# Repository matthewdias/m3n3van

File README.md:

# m3n3van
 
- The rev1 pcb supports a lot of different layouts. This was mostly an exercise for me and a way to make some unique bottom rows available that wouldn't exist otherwise. As a result it has a few issues, a missing switch, and lots of conflicts with screw holes, necessitating switch rotation.

- The rev2 pcb is a return to the original idea of simply a minivan with 2x3u split space.

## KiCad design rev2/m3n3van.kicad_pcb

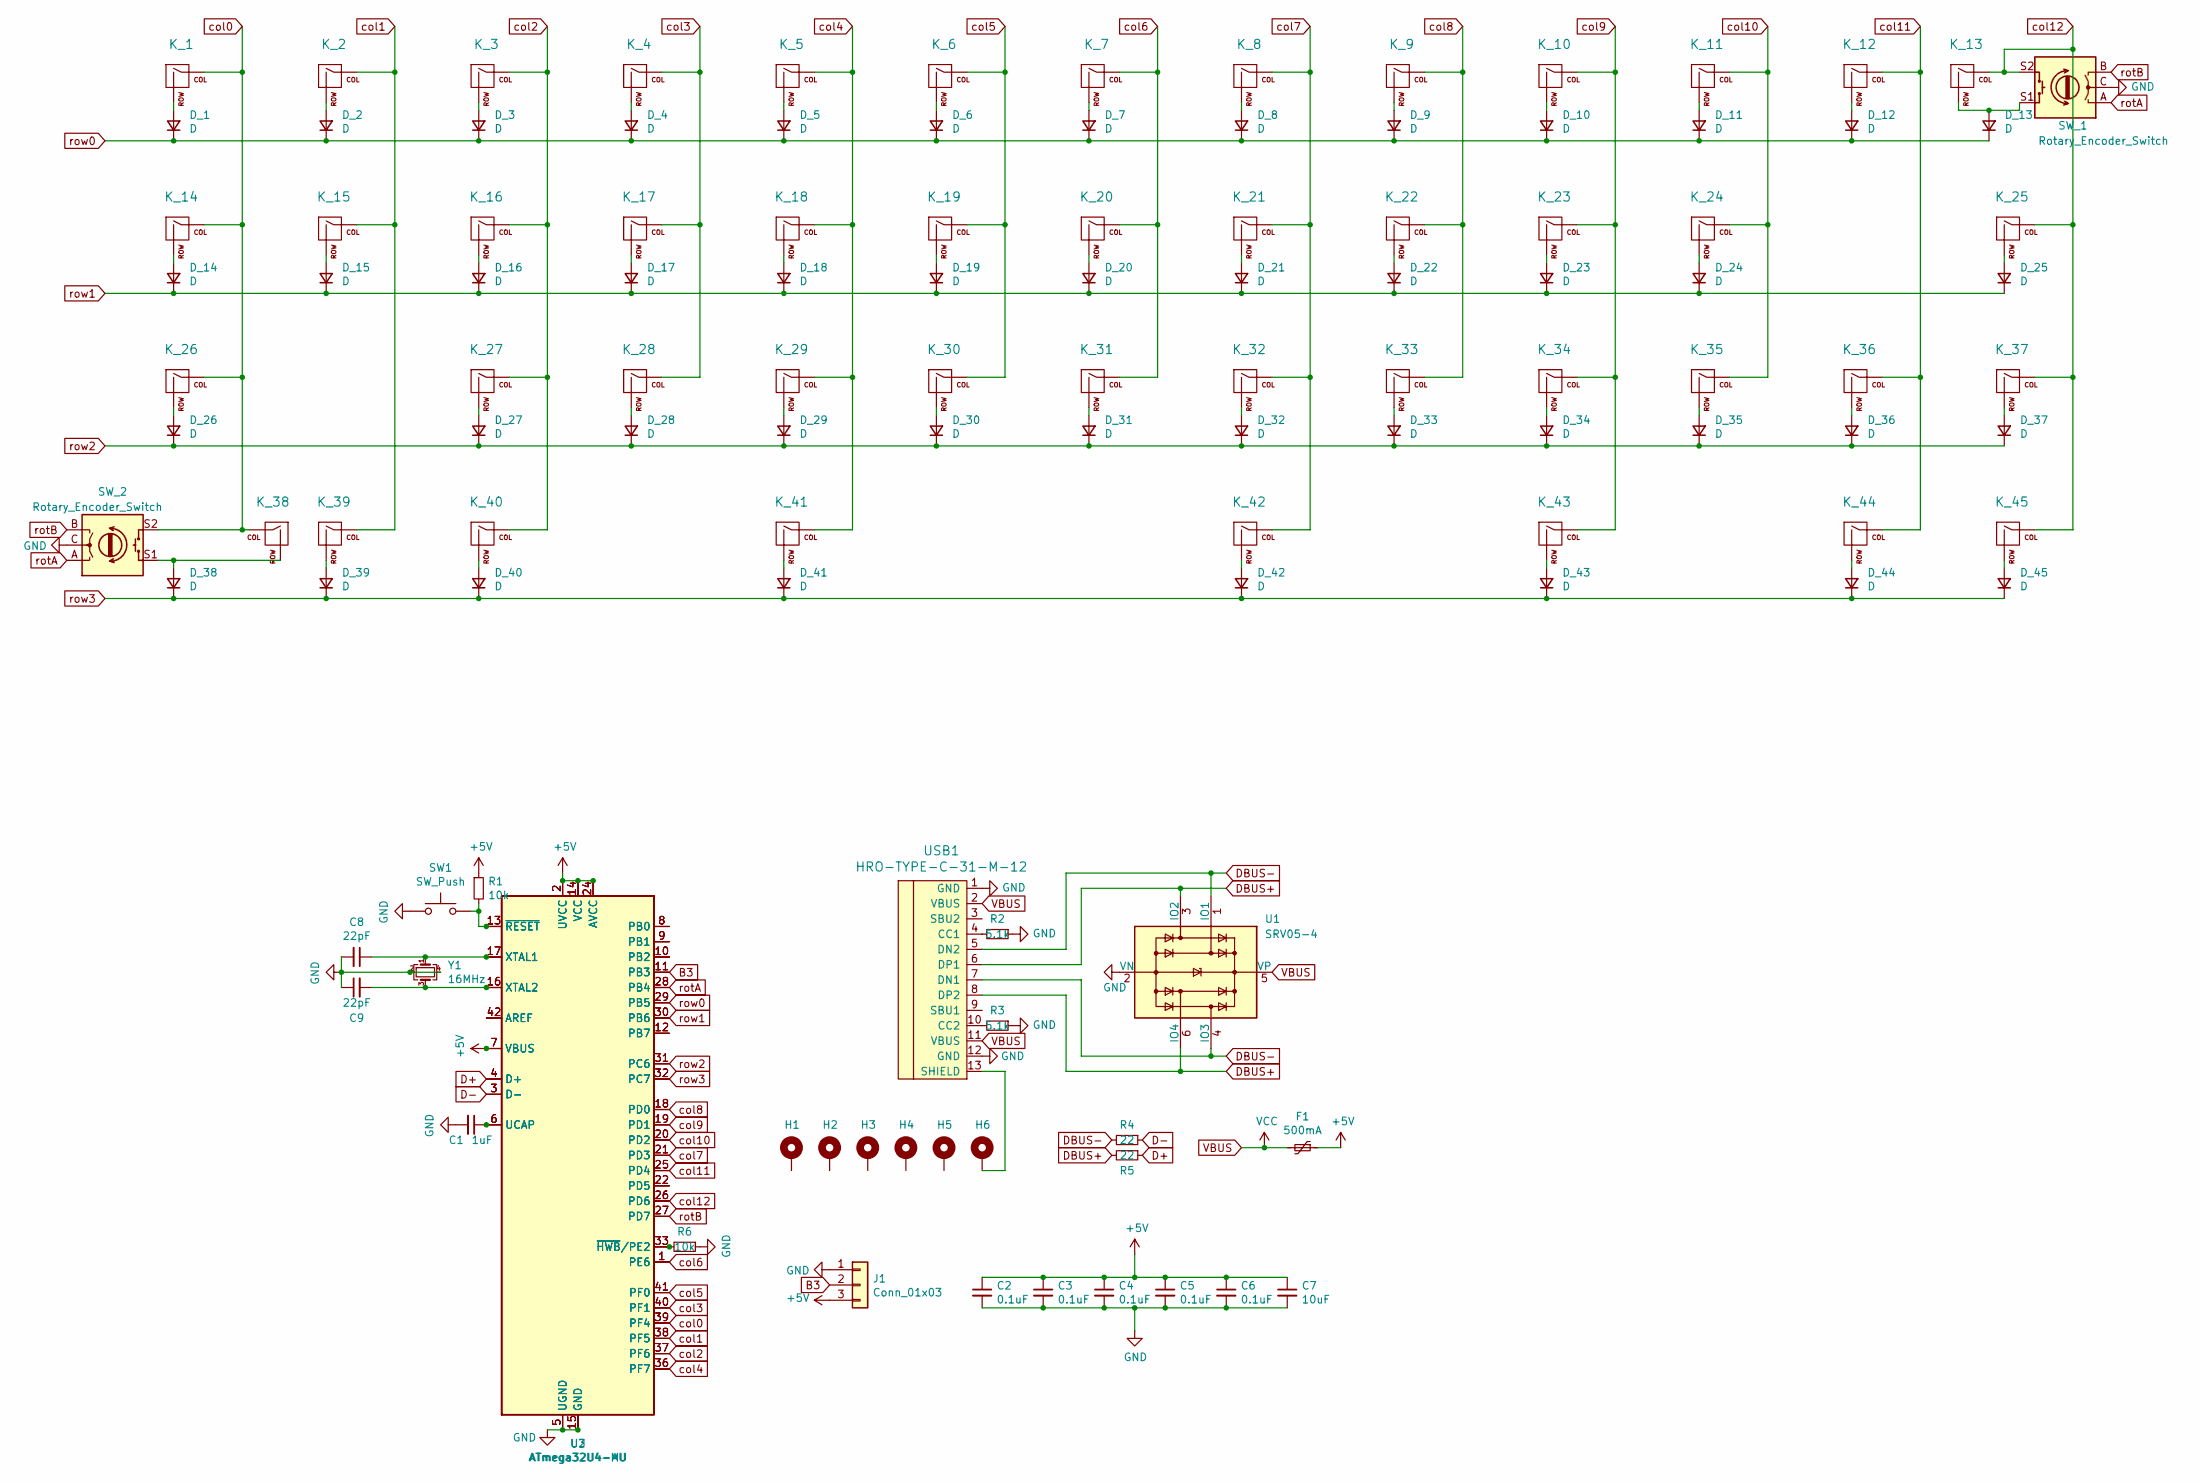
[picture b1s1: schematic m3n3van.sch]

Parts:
C1: 1uF; C_0603_1608Metric
C2, C3, C4, C5, C6: 0.1uF; C_0603_1608Metric
C7: 10uF; C_0603_1608Metric
C8, C9: 22pF; C_0603_1608Metric
D_1, D_2, D_3, D_4, D_5, D_6, D_7, D_8, D_9, D_10, D_11, D_12, D_13, D_14, D_15, D_16, D_17, D_18, D_19, D_20, D_21, D_22, D_23, D_24, D_25, D_26, D_27, D_28, D_29, D_30, D_31, D_32, D_33, D_34, D_35, D_36, D_37, D_38, D_39, D_40, D_41, D_42, D_43, D_44, D_45: D; D_SOD-123
F1: 500mA; Fuse_1206_3216Metric
H1, H2, H3, H4, H5, H6: MountingHole_Pad; MountingHole_2.2mm_M2_Pad
J1: Conn_01x03; PinHeader_1x03_P2.54mm_Vertical
K_1, K_2, K_3, K_4, K_5, K_6, K_7, K_8, K_9, K_10, K_11, K_12, K_15, K_16, K_17, K_18, K_19, K_20, K_21, K_22, K_23, K_24, K_27, K_28, K_29, K_30, K_31, K_32, K_33, K_34, K_35, K_36, K_37, K_38, K_40, K_44: KEYSW; MXOnly-1U-NoLED
K_13, K_26: KEYSW; MXOnly-1.75U-NoLED
K_14, K_39, K_43, K_45: KEYSW; MXOnly-1.25U-NoLED
K_25: KEYSW; MXOnly-1.5U-NoLED
K_41, K_42: KEYSW; MXOnly-3U-ReversedStabilizers-NoLED
R1, R6: 10k; R_0603_1608Metric
R2, R3: 5.1k; R_0603_1608Metric
R4, R5: 22; R_0603_1608Metric
SW1: SW_Push; SW_Push_SPST_NO_Alps_SKRK
SW_1, SW_2: Rotary_Encoder_Switch; RotaryEncoder_Alps_EC11E-Switch_Vertical_H20mm
U1: SRV05-4; SOT-23-6
U2: ATmega32U4-AU; TQFP-44_10x10mm_P0.8mm
U3: ATmega32U4-MU; QFN-44-1EP_7x7mm_P0.5mm_EP5.2x5.2mm
USB1: HRO-TYPE-C-31-M-12; HRO-TYPE-C-31-M-12-Assembly
Y1: 16MHz; Crystal_SMD_3225-4Pin_3.2x2.5mm

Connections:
+5V: C2.1, C3.1, C4.1, C5.1, C6.1, C7.1, F1.1, J1.3, R1.1, U2.2 (UVCC), U2.7 (VBUS), U2.14 (VCC), U2.24 (AVCC), U2.34 (VCC), U2.44 (AVCC), U3.2 (UVCC), U3.7 (VBUS), U3.14 (VCC), U3.24 (AVCC), U3.34 (VCC), U3.44 (AVCC)
B3: J1.2, U2.11 (PB3), U3.11 (PB3)
D+: R5.1, U2.4 (D+), U3.4 (D+)
D-: R4.1, U2.3 (D-), U3.3 (D-)
DBUS+: R5.2, U1.3 (IO2), U1.6 (IO4), USB1.6 (DP1), USB1.8 (DP2)
DBUS-: R4.2, U1.1 (IO1), U1.4 (IO3), USB1.5 (DN2), USB1.7 (DN1)
GND: C1.2, C2.2, C3.2, C4.2, C5.2, C6.2, C7.2, C8.2, C9.1, J1.1, R2.1, R3.1, R6.1, SW1.1, SW_1.C, SW_2.C, U1.2 (VN), U2.5 (UGND), U2.15 (GND), U2.23 (GND), U2.35 (GND), U2.43 (GND), U3.5 (UGND), U3.15 (GND), U3.23 (GND), U3.35 (GND), U3.43 (GND), U3.45 (GND), USB1.1 (GND), USB1.12 (GND), Y1.2, Y1.4
unnamed: C1.1, U2.6 (UCAP), U3.6 (UCAP)
unnamed: C8.1, U2.17 (XTAL1), U3.17 (XTAL1), Y1.1
unnamed: C9.2, U2.16 (XTAL2), U3.16 (XTAL2), Y1.3
unnamed: D_1.2 (A), K_1.2 (ROW)
unnamed: D_2.2 (A), K_2.2 (ROW)
unnamed: D_3.2 (A), K_3.2 (ROW)
unnamed: D_4.2 (A), K_4.2 (ROW)
unnamed: D_5.2 (A), K_5.2 (ROW)
unnamed: D_6.2 (A), K_6.2 (ROW)
unnamed: D_7.2 (A), K_7.2 (ROW)
unnamed: D_8.2 (A), K_8.2 (ROW)
unnamed: D_9.2 (A), K_9.2 (ROW)
unnamed: D_10.2 (A), K_10.2 (ROW)
unnamed: D_11.2 (A), K_11.2 (ROW)
unnamed: D_12.2 (A), K_12.2 (ROW)
unnamed: D_13.2 (A), K_13.2 (ROW), SW_1.S1
unnamed: D_14.2 (A), K_14.2 (ROW)
unnamed: D_15.2 (A), K_15.2 (ROW)
unnamed: D_16.2 (A), K_16.2 (ROW)
unnamed: D_17.2 (A), K_17.2 (ROW)
unnamed: D_18.2 (A), K_18.2 (ROW)
unnamed: D_19.2 (A), K_19.2 (ROW)
unnamed: D_20.2 (A), K_20.2 (ROW)
unnamed: D_21.2 (A), K_21.2 (ROW)
unnamed: D_22.2 (A), K_22.2 (ROW)
unnamed: D_23.2 (A), K_23.2 (ROW)
unnamed: D_24.2 (A), K_24.2 (ROW)
unnamed: D_25.2 (A), K_25.2 (ROW)
unnamed: D_26.2 (A), K_26.2 (ROW)
unnamed: D_27.2 (A), K_27.2 (ROW)
unnamed: D_28.2 (A), K_28.2 (ROW)
unnamed: D_29.2 (A), K_29.2 (ROW)
unnamed: D_30.2 (A), K_30.2 (ROW)
unnamed: D_31.2 (A), K_31.2 (ROW)
unnamed: D_32.2 (A), K_32.2 (ROW)
unnamed: D_33.2 (A), K_33.2 (ROW)
unnamed: D_34.2 (A), K_34.2 (ROW)
unnamed: D_35.2 (A), K_35.2 (ROW)
unnamed: D_36.2 (A), K_36.2 (ROW)
unnamed: D_37.2 (A), K_37.2 (ROW)
unnamed: D_38.2 (A), K_38.2 (ROW), SW_2.S1
unnamed: D_39.2 (A), K_39.2 (ROW)
unnamed: D_40.2 (A), K_40.2 (ROW)
unnamed: D_41.2 (A), K_41.2 (ROW)
unnamed: D_42.2 (A), K_42.2 (ROW)
unnamed: D_43.2 (A), K_43.2 (ROW)
unnamed: D_44.2 (A), K_44.2 (ROW)
unnamed: D_45.2 (A), K_45.2 (ROW)
unnamed: H6.1, USB1.13 (SHIELD)
unnamed: R1.2, SW1.2, U2.13 (~RESET), U3.13 (~RESET)
unnamed: R2.2, USB1.4 (CC1)
unnamed: R3.2, USB1.10 (CC2)
unnamed: R6.2, U2.33 (~HWB~/PE2), U3.33 (~HWB~/PE2)
unnamed: U2.8 (PB0), U3.8 (PB0)
unnamed: U2.9 (PB1), U3.9 (PB1)
unnamed: U2.10 (PB2), U3.10 (PB2)
unnamed: U2.12 (PB7), U3.12 (PB7)
unnamed: U2.22 (PD5), U3.22 (PD5)
unnamed: U2.42 (AREF), U3.42 (AREF)
VBUS: F1.2, U1.5 (VP), USB1.2 (VBUS), USB1.11 (VBUS)
col0: K_1.1 (COL), K_14.1 (COL), K_26.1 (COL), K_38.1 (COL), SW_2.S2, U2.39 (PF4), U3.39 (PF4)
col1: K_2.1 (COL), K_15.1 (COL), K_39.1 (COL), U2.38 (PF5), U3.38 (PF5)
col2: K_3.1 (COL), K_16.1 (COL), K_27.1 (COL), K_40.1 (COL), U2.37 (PF6), U3.37 (PF6)
col3: K_4.1 (COL), K_17.1 (COL), K_28.1 (COL), U2.40 (PF1), U3.40 (PF1)
col4: K_5.1 (COL), K_18.1 (COL), K_29.1 (COL), K_41.1 (COL), U2.36 (PF7), U3.36 (PF7)
col5: K_6.1 (COL), K_19.1 (COL), K_30.1 (COL), U2.41 (PF0), U3.41 (PF0)
col6: K_7.1 (COL), K_20.1 (COL), K_31.1 (COL), U2.1 (PE6), U3.1 (PE6)
col7: K_8.1 (COL), K_21.1 (COL), K_32.1 (COL), K_42.1 (COL), U2.21 (PD3), U3.21 (PD3)
col8: K_9.1 (COL), K_22.1 (COL), K_33.1 (COL), U2.18 (PD0), U3.18 (PD0)
col9: K_10.1 (COL), K_23.1 (COL), K_34.1 (COL), K_43.1 (COL), U2.19 (PD1), U3.19 (PD1)
col10: K_11.1 (COL), K_24.1 (COL), K_35.1 (COL), U2.20 (PD2), U3.20 (PD2)
col11: K_12.1 (COL), K_36.1 (COL), K_44.1 (COL), U2.25 (PD4), U3.25 (PD4)
col12: K_13.1 (COL), K_25.1 (COL), K_37.1 (COL), K_45.1 (COL), SW_1.S2, U2.26 (PD6), U3.26 (PD6)
rotA: SW_1.A, SW_2.A, U2.28 (PB4), U3.28 (PB4)
rotB: SW_1.B, SW_2.B, U2.27 (PD7), U3.27 (PD7)
row0: D_1.1 (K), D_2.1 (K), D_3.1 (K), D_4.1 (K), D_5.1 (K), D_6.1 (K), D_7.1 (K), D_8.1 (K), D_9.1 (K), D_10.1 (K), D_11.1 (K), D_12.1 (K), D_13.1 (K), U2.29 (PB5), U3.29 (PB5)
row1: D_14.1 (K), D_15.1 (K), D_16.1 (K), D_17.1 (K), D_18.1 (K), D_19.1 (K), D_20.1 (K), D_21.1 (K), D_22.1 (K), D_23.1 (K), D_24.1 (K), D_25.1 (K), U2.30 (PB6), U3.30 (PB6)
row2: D_26.1 (K), D_27.1 (K), D_28.1 (K), D_29.1 (K), D_30.1 (K), D_31.1 (K), D_32.1 (K), D_33.1 (K), D_34.1 (K), D_35.1 (K), D_36.1 (K), D_37.1 (K), U2.31 (PC6), U3.31 (PC6)
row3: D_38.1 (K), D_39.1 (K), D_40.1 (K), D_41.1 (K), D_42.1 (K), D_43.1 (K), D_44.1 (K), D_45.1 (K), U2.32 (PC7), U3.32 (PC7)

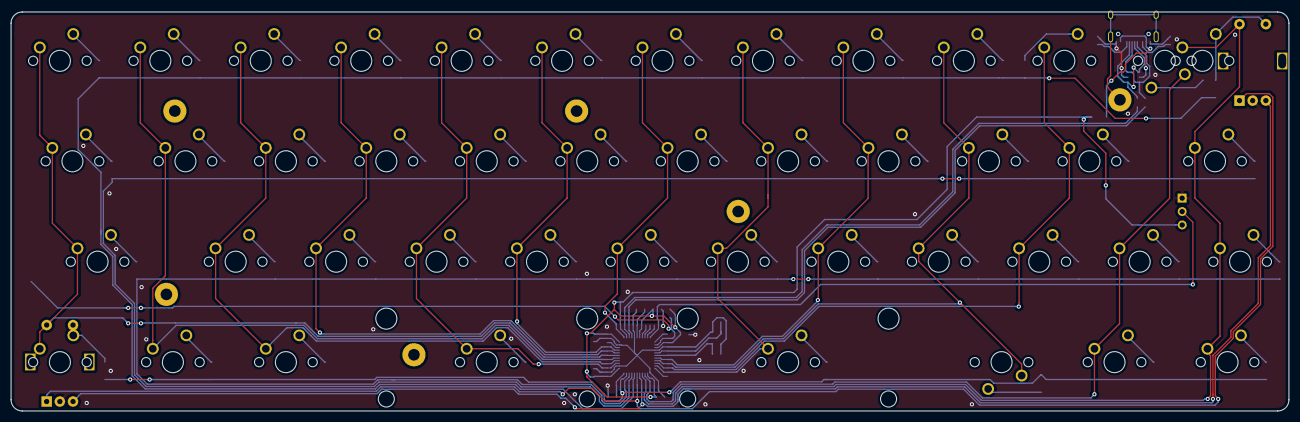
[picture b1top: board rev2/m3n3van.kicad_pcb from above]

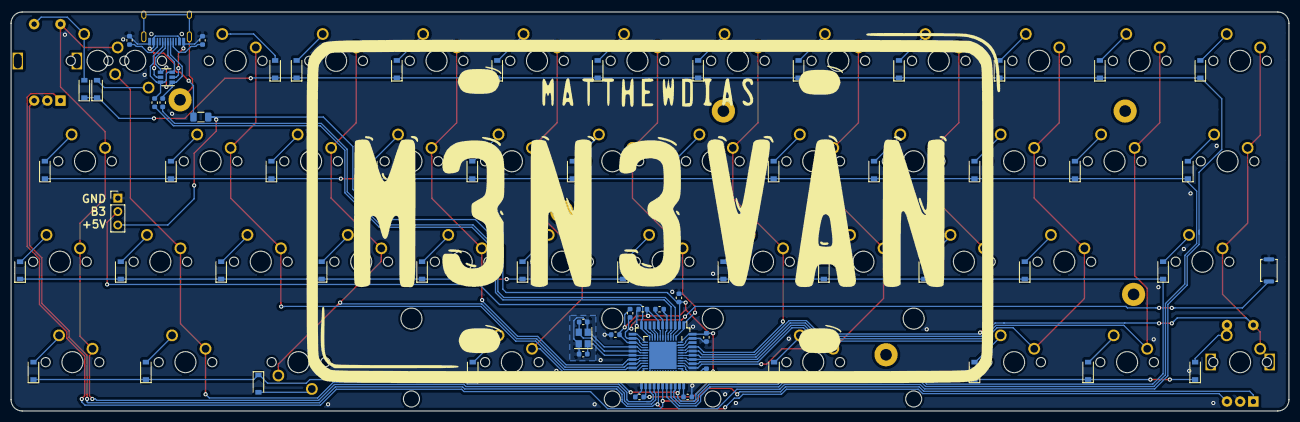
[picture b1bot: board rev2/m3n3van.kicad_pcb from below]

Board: 2 copper layers, 242.4 x 75.7 mm, 121 parts (68 on the bottom side), 86 nets.

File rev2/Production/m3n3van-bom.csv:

"Designator","Quantity",Value,Footprint,LCSC Part #
"C1, ","1",1uF,0603,C15849
"C2, C3, C4, C5, C6, ","5",0.1uF,0603,C14663
"C7, ","1",10uF,0603,C19702
"C8, C9, ","2",22pF,0603,C1653
"D_1, D_2, D_3, D_4, D_5, D_6, D_7, D_8, D_9, D_10, D_11, D_12, D_13, D_14, D_15, D_16, D_17, D_18, D_19, D_20, D_21, D_22, D_23, D_24, D_25, D_26, D_27, D_28, D_29, D_30, D_31, D_32, D_33, D_34, D_35, D_36, D_37, D_38, D_39, D_40, D_41, D_42, D_43, D_44, D_45, ","45",D,SOD-123,C64898
"F1, ","1",500mA,1206,C70076
"R1, R6, ","2",10k,0603,C25804
"R2, R3, ","2",5.1k,0603,C23186
"R4, R5, ","2",22,0603,C23345
"SW1, ","1",SW_Push,SMD,C561519
"U1, ","1",SRV05-4,SOT-23-6,C558454
"U3, ","1",ATmega32U4-MU,QFN-44,C45874
"USB1, ","1",HRO-TYPE-C-31-M-12,HRO-TYPE-C-31-M-12,C165948
"Y1, ","1",16MHz,3225,C13738

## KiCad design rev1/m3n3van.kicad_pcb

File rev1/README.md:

## Layout Options

Configure firmware at https://qmk.thevankeyboards.com/

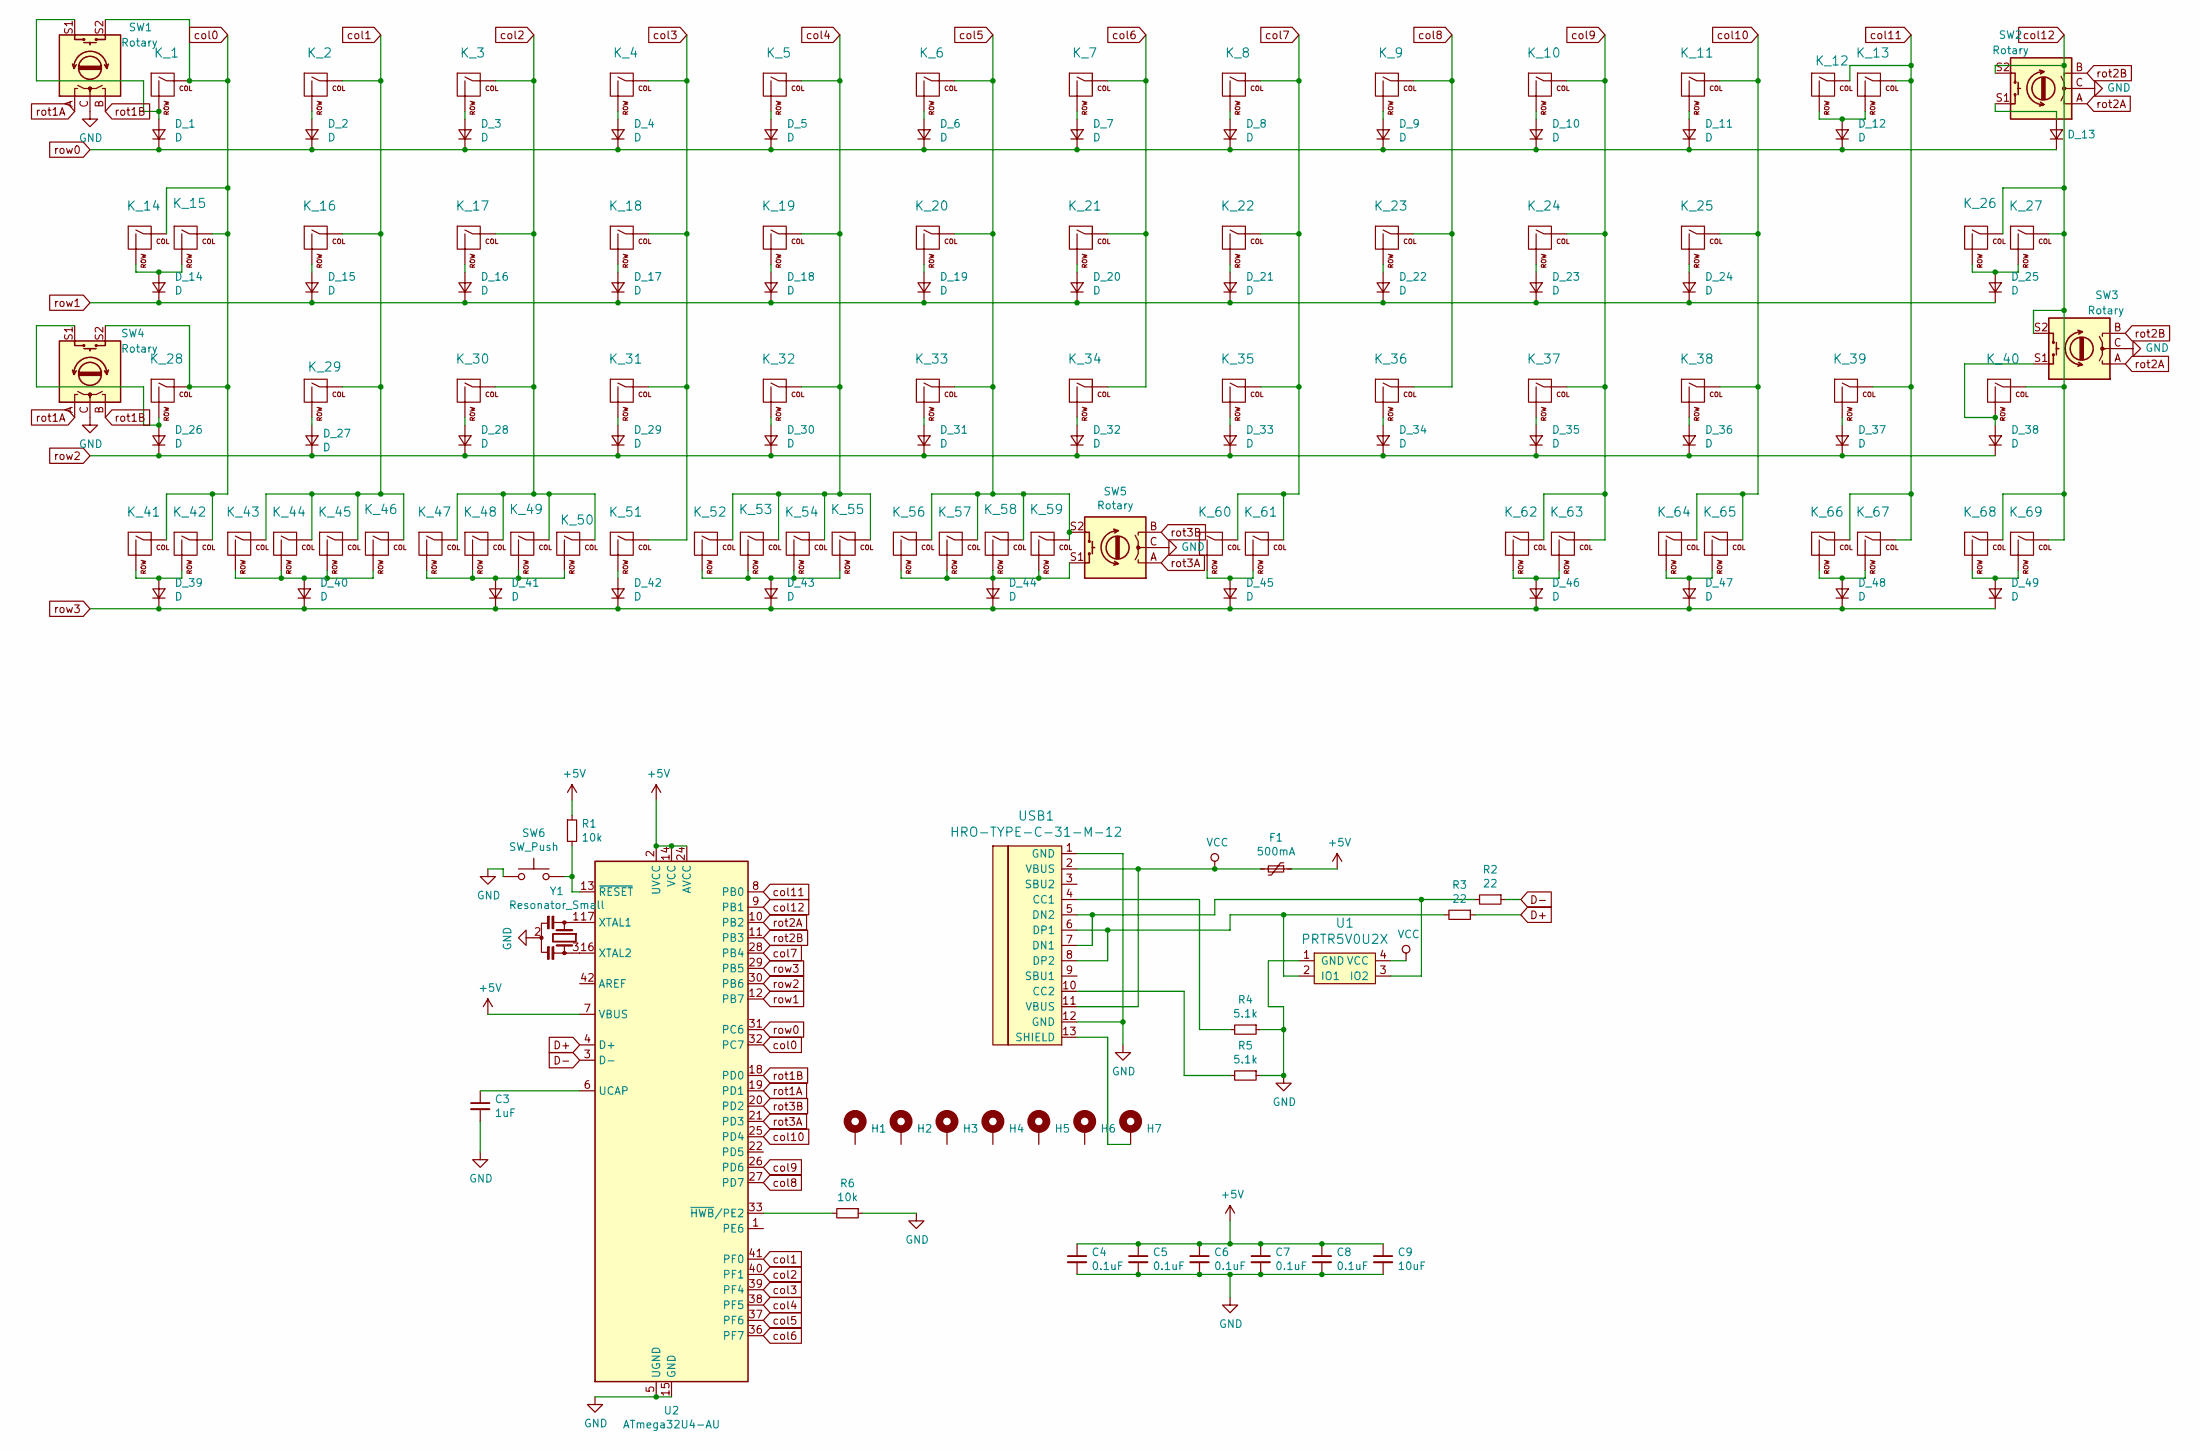
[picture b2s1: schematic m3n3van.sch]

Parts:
C3: 1uF; C_0805_2012Metric
C4, C5, C6, C7, C8: 0.1uF; C_0805_2012Metric
C9: 10uF; C_0805_2012Metric
D_1, D_2, D_3, D_4, D_5, D_6, D_7, D_8, D_9, D_10, D_11, D_12, D_13, D_14, D_15, D_16, D_17, D_18, D_19, D_20, D_21, D_22, D_23, D_24, D_25, D_26, D_27, D_28, D_29, D_30, D_31, D_32, D_33, D_34, D_35, D_36, D_37, D_38, D_39, D_40, D_41, D_42, D_43, D_44, D_45, D_46, D_47, D_48, D_49: D; D_SOD-123
F1: 500mA; Fuse_1206_3216Metric
H1, H2, H3, H4, H5, H6, H7: MountingHole_Pad; MountingHole_2.2mm_M2_Pad
K_1, K_2, K_3, K_4, K_5, K_6, K_7, K_8, K_9, K_10, K_11, K_12, K_15, K_16, K_17, K_18, K_19, K_20, K_21, K_22, K_23, K_24, K_25, K_26, K_29, K_30, K_31, K_32, K_33, K_34, K_35, K_36, K_37, K_38, K_39, K_40, K_41, K_43, K_45, K_47, K_48, K_51, K_53, K_63, K_65, K_66, K_67, K_69: KEYSW; MXOnly-1U-NoLED
K_13, K_28: KEYSW; MXOnly-1.75U-NoLED
K_14, K_42, K_44, K_46, K_49, K_50, K_52, K_62, K_64, K_68: KEYSW; MXOnly-1.25U-NoLED
K_27: KEYSW; MXOnly-1.5U-NoLED
K_54: KEYSW; MXOnly-3U-ReversedStabilizers-NoLED
K_55, K_57, K_60: KEYSW; MXOnly-2U-NoStab-NoLED
K_56: KEYSW; MXOnly-2.75U-ReversedStabilizers-NoLED
K_58: KEYSW; MXOnly-6U-Centered-3U-ReversedStabilizers-NoLED
K_59: KEYSW; MXOnly-5U-ReversedStabilizers-NoLED
K_61: KEYSW; MXOnly-3U-2U-ReversedStabilizers-NoLED
R1, R6: 10k; R_0805_2012Metric
R2, R3: 22; R_0805_2012Metric
R4, R5: 5.1k; R_0805_2012Metric
SW1, SW2, SW3, SW4, SW5: Rotary; RotaryEncoder_Alps_EC11E-Switch_Vertical_H20mm
SW6: SW_Push; SW_Push_1P1T_NO_CK_KMR2
U1: PRTR5V0U2X; SOT143B
U2: ATmega32U4-AU; TQFP-44_10x10mm_P0.8mm
USB1: HRO-TYPE-C-31-M-12; HRO-TYPE-C-31-M-12-Assembly
Y1: Resonator_Small; Resonator_SMD_muRata_CSTxExxV-3Pin_3.0x1.1mm_HandSoldering

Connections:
+5V: C4.1, C5.1, C6.1, C7.1, C8.1, C9.1, F1.1, R1.1, U2.2 (UVCC), U2.7 (VBUS), U2.14 (VCC), U2.24 (AVCC), U2.34 (VCC), U2.44 (AVCC)
D+: R3.1, U2.4 (D+)
D-: R2.1, U2.3 (D-)
GND: C3.2, C4.2, C5.2, C6.2, C7.2, C8.2, C9.2, R4.1, R5.1, R6.1, SW1.C, SW2.C, SW3.C, SW4.C, SW5.C, SW6.1, U1.1 (GND), U2.5 (UGND), U2.15 (GND), U2.23 (GND), U2.35 (GND), U2.43 (GND), USB1.1 (GND), USB1.12 (GND), Y1.2
unnamed: C3.1, U2.6 (UCAP)
unnamed: D_1.2 (A), K_1.2 (ROW), SW1.S1
unnamed: D_2.2 (A), K_2.2 (ROW)
unnamed: D_3.2 (A), K_3.2 (ROW)
unnamed: D_4.2 (A), K_4.2 (ROW)
unnamed: D_5.2 (A), K_5.2 (ROW)
unnamed: D_6.2 (A), K_6.2 (ROW)
unnamed: D_7.2 (A), K_7.2 (ROW)
unnamed: D_8.2 (A), K_8.2 (ROW)
unnamed: D_9.2 (A), K_9.2 (ROW)
unnamed: D_10.2 (A), K_10.2 (ROW)
unnamed: D_11.2 (A), K_11.2 (ROW)
unnamed: D_12.2 (A), K_12.2 (ROW), K_13.2 (ROW)
unnamed: D_13.2 (A), SW2.S1
unnamed: D_14.2 (A), K_14.2 (ROW), K_15.2 (ROW)
unnamed: D_15.2 (A), K_16.2 (ROW)
unnamed: D_16.2 (A), K_17.2 (ROW)
unnamed: D_17.2 (A), K_18.2 (ROW)
unnamed: D_18.2 (A), K_19.2 (ROW)
unnamed: D_19.2 (A), K_20.2 (ROW)
unnamed: D_20.2 (A), K_21.2 (ROW)
unnamed: D_21.2 (A), K_22.2 (ROW)
unnamed: D_22.2 (A), K_23.2 (ROW)
unnamed: D_23.2 (A), K_24.2 (ROW)
unnamed: D_24.2 (A), K_25.2 (ROW)
unnamed: D_25.2 (A), K_26.2 (ROW), K_27.2 (ROW)
unnamed: D_26.2 (A), K_28.2 (ROW), SW4.S1
unnamed: D_27.2 (A), K_29.2 (ROW)
unnamed: D_28.2 (A), K_30.2 (ROW)
unnamed: D_29.2 (A), K_31.2 (ROW)
unnamed: D_30.2 (A), K_32.2 (ROW)
unnamed: D_31.2 (A), K_33.2 (ROW)
unnamed: D_32.2 (A), K_34.2 (ROW)
unnamed: D_33.2 (A), K_35.2 (ROW)
unnamed: D_34.2 (A), K_36.2 (ROW)
unnamed: D_35.2 (A), K_37.2 (ROW)
unnamed: D_36.2 (A), K_38.2 (ROW)
unnamed: D_37.2 (A), K_39.2 (ROW)
unnamed: D_38.2 (A), K_40.2 (ROW), SW3.S1
unnamed: D_39.2 (A), K_41.2 (ROW), K_42.2 (ROW)
unnamed: D_40.2 (A), K_43.2 (ROW), K_44.2 (ROW), K_45.2 (ROW), K_46.2 (ROW)
unnamed: D_41.2 (A), K_47.2 (ROW), K_48.2 (ROW), K_49.2 (ROW), K_50.2 (ROW)
unnamed: D_42.2 (A), K_51.2 (ROW)
unnamed: D_43.2 (A), K_52.2 (ROW), K_53.2 (ROW), K_54.2 (ROW), K_55.2 (ROW)
unnamed: D_44.2 (A), K_56.2 (ROW), K_57.2 (ROW), K_58.2 (ROW), K_59.2 (ROW), SW5.S1
unnamed: D_45.2 (A), K_60.2 (ROW), K_61.2 (ROW)
unnamed: D_46.2 (A), K_62.2 (ROW), K_63.2 (ROW)
unnamed: D_47.2 (A), K_64.2 (ROW), K_65.2 (ROW)
unnamed: D_48.2 (A), K_66.2 (ROW), K_67.2 (ROW)
unnamed: D_49.2 (A), K_68.2 (ROW), K_69.2 (ROW)
unnamed: H7.1, USB1.13 (SHIELD)
unnamed: R1.2, SW6.2, U2.13 (~RESET)
unnamed: R2.2, U1.3 (IO2), USB1.5 (DN2), USB1.7 (DN1)
unnamed: R3.2, U1.2 (IO1), USB1.6 (DP1), USB1.8 (DP2)
unnamed: R4.2, USB1.4 (CC1)
unnamed: R5.2, USB1.10 (CC2)
unnamed: R6.2, U2.33 (~HWB~/PE2)
unnamed: U2.16 (XTAL2), Y1.3
unnamed: U2.17 (XTAL1), Y1.1
VCC: F1.2, U1.4 (VCC), USB1.2 (VBUS), USB1.11 (VBUS)
col0: K_1.1 (COL), K_14.1 (COL), K_15.1 (COL), K_28.1 (COL), K_41.1 (COL), K_42.1 (COL), SW1.S2, SW4.S2, U2.32 (PC7)
col1: K_2.1 (COL), K_16.1 (COL), K_29.1 (COL), K_43.1 (COL), K_44.1 (COL), K_45.1 (COL), K_46.1 (COL), U2.41 (PF0)
col2: K_3.1 (COL), K_17.1 (COL), K_30.1 (COL), K_47.1 (COL), K_48.1 (COL), K_49.1 (COL), K_50.1 (COL), U2.40 (PF1)
col3: K_4.1 (COL), K_18.1 (COL), K_31.1 (COL), K_51.1 (COL), U2.39 (PF4)
col4: K_5.1 (COL), K_19.1 (COL), K_32.1 (COL), K_52.1 (COL), K_53.1 (COL), K_54.1 (COL), K_55.1 (COL), U2.38 (PF5)
col5: K_6.1 (COL), K_20.1 (COL), K_33.1 (COL), K_56.1 (COL), K_57.1 (COL), K_58.1 (COL), K_59.1 (COL), SW5.S2, U2.37 (PF6)
col6: K_7.1 (COL), K_21.1 (COL), K_34.1 (COL), U2.36 (PF7)
col7: K_8.1 (COL), K_22.1 (COL), K_35.1 (COL), K_60.1 (COL), K_61.1 (COL), U2.28 (PB4)
col8: K_9.1 (COL), K_23.1 (COL), K_36.1 (COL), U2.27 (PD7)
col9: K_10.1 (COL), K_24.1 (COL), K_37.1 (COL), K_62.1 (COL), K_63.1 (COL), U2.26 (PD6)
col10: K_11.1 (COL), K_25.1 (COL), K_38.1 (COL), K_64.1 (COL), K_65.1 (COL), U2.25 (PD4)
col11: K_12.1 (COL), K_13.1 (COL), K_39.1 (COL), K_66.1 (COL), K_67.1 (COL), U2.8 (PB0)
col12: K_26.1 (COL), K_27.1 (COL), K_40.1 (COL), K_68.1 (COL), K_69.1 (COL), SW2.S2, SW3.S2, U2.9 (PB1)
rot1A: SW1.A, SW4.A, U2.19 (PD1)
rot1B: SW1.B, SW4.B, U2.18 (PD0)
rot2A: SW2.A, SW3.A, U2.10 (PB2)
rot2B: SW2.B, SW3.B, U2.11 (PB3)
rot3A: SW5.A, U2.21 (PD3)
rot3B: SW5.B, U2.20 (PD2)
row0: D_1.1 (K), D_2.1 (K), D_3.1 (K), D_4.1 (K), D_5.1 (K), D_6.1 (K), D_7.1 (K), D_8.1 (K), D_9.1 (K), D_10.1 (K), D_11.1 (K), D_12.1 (K), D_13.1 (K), U2.31 (PC6)
row1: D_14.1 (K), D_15.1 (K), D_16.1 (K), D_17.1 (K), D_18.1 (K), D_19.1 (K), D_20.1 (K), D_21.1 (K), D_22.1 (K), D_23.1 (K), D_24.1 (K), D_25.1 (K), U2.12 (PB7)
row2: D_26.1 (K), D_27.1 (K), D_28.1 (K), D_29.1 (K), D_30.1 (K), D_31.1 (K), D_32.1 (K), D_33.1 (K), D_34.1 (K), D_35.1 (K), D_36.1 (K), D_37.1 (K), D_38.1 (K), U2.30 (PB6)
row3: D_39.1 (K), D_40.1 (K), D_41.1 (K), D_42.1 (K), D_43.1 (K), D_44.1 (K), D_45.1 (K), D_46.1 (K), D_47.1 (K), D_48.1 (K), D_49.1 (K), U2.29 (PB5)

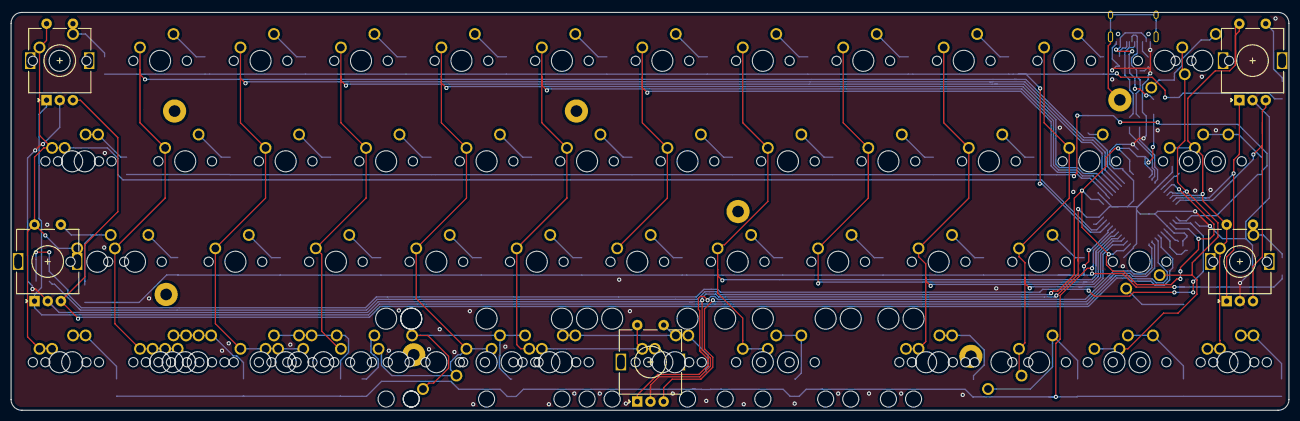
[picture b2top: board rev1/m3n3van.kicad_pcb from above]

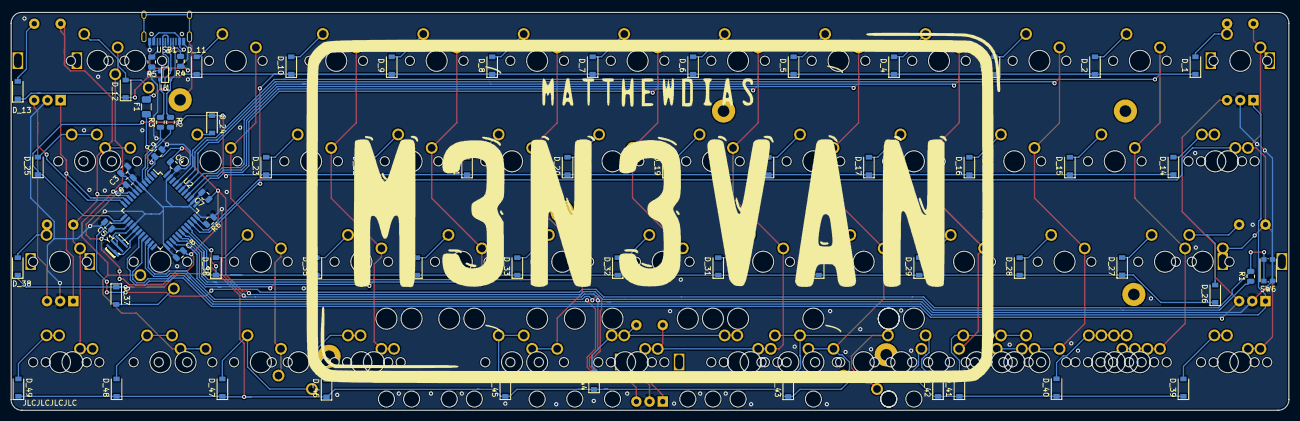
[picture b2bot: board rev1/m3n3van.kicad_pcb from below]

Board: 2 copper layers, 242.3 x 75.4 mm, 149 parts (68 on the bottom side), 87 nets.

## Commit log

2020-11-30 Add rev2 PCB
2020-11-30 Address review feedback
2020-12-13 Add rev1 pcb
2020-12-13 Update rev2 for production
2020-12-13 Add readmes
2020-12-21 Add plate files
2021-01-31 Add Coriander plate
2021-03-18 Add second encoder, RGB header, switch to assembly resonator footprint
2021-03-18 Fix plate encoder cutouts
2021-03-18 Update components, production files
2022-01-17 Add usb to rev1 production files
2022-01-17 Switch to crystal, add MU dual footprint
2022-01-17 Add campsite plates
